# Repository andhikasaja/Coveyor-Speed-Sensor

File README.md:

# Coveyor-Speed-Sensor
Repository untuk pengukur kecepatan motor konveyor dengan lm393 dan optocoupler

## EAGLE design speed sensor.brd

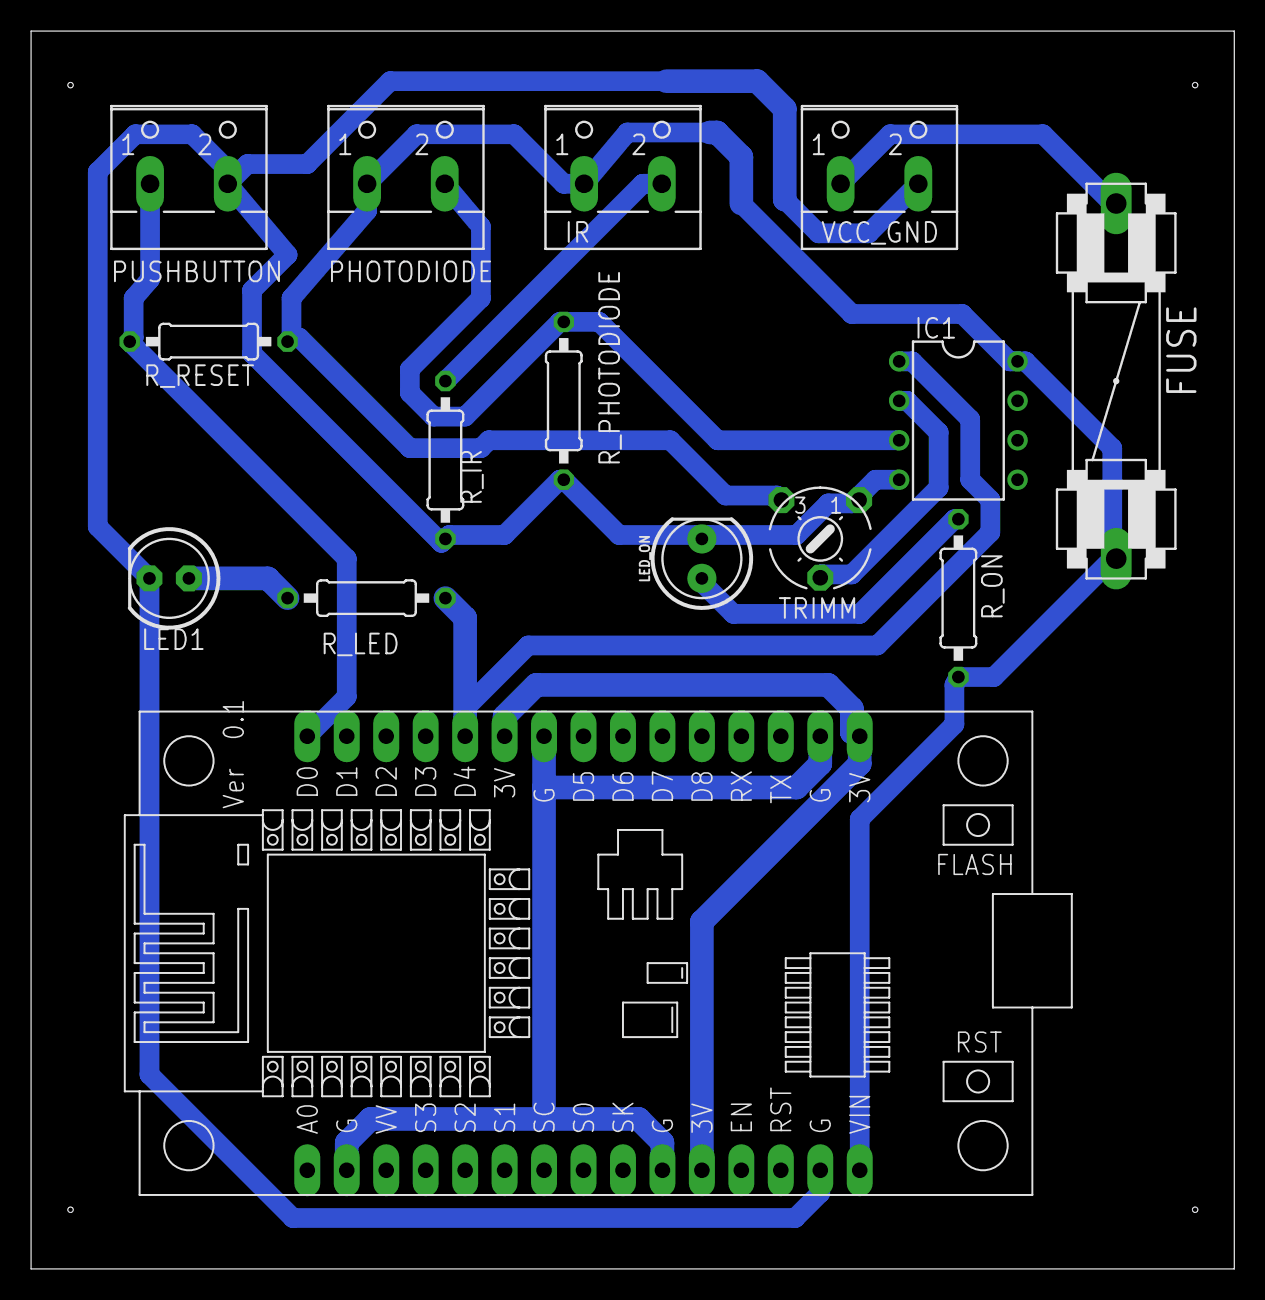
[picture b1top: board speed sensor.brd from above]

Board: 2 copper layers, 77.5 x 79.7 mm, 15 parts (0 on the bottom side), 12 nets.

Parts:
FUSE: 1 amp; FUSE
IC1: LM358N; DIL08
IR: W237-102
LED1: LED5MM
LED_ON: LED_5MM
PHOTODIODE: W237-102
PUSHBUTTON: W237-102
R_IR: 100; 0207/10
R_LED: 330; 0207/10
R_ON: 330; 0207/10
R_PHOTODIODE: 10k; 0207/10
R_RESET: 10k; 0207/10
TRIMM: 10k; 6MM
U$1: NODEMCU
VCC_GND: W237-102

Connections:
3V: U$1.11, U$1.16, U$1.25
GND: IC1.4, LED1.K, LED_ON.K, PUSHBUTTON.2, R_IR.1, R_PHOTODIODE.1, TRIMM.A, U$1.14, VCC_GND.2
unnamed: LED1.A, R_LED.1
unnamed: IR.2, R_IR.2
unnamed: U$1.2, U$1.10, U$1.17, U$1.24
unnamed: IC1.3, PHOTODIODE.2, R_PHOTODIODE.2
unnamed: IC1.2, TRIMM.S
unnamed: IC1.1, R_LED.2, U$1.26
unnamed: PUSHBUTTON.1, R_RESET.2, U$1.30
unnamed: LED_ON.A, R_ON.1
unnamed: FUSE.2, IC1.8, IR.1, PHOTODIODE.1, R_ON.2, R_RESET.1, TRIMM.E, U$1.15
VCC: FUSE.1, VCC_GND.1

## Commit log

2019-11-04 versi 0.1 untuk sensor kecepatan
2019-11-04 versi 0.2 revisi variabel rps >> rpm
2019-11-04 penambahan fitur apabila beban terlalu berat, muncul peringatan
2019-11-04 0.4 update lcd menggunakan i2c
2019-11-24 perubahan skematik counter. Penambahan terminal block
2019-12-04 board rev 5

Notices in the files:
parts and their libraries:
SparkFun-LED: Licensing: Creative Commons ShareAlike 4.0 International - https://creativecommons.org/licenses/by-sa/4.0
